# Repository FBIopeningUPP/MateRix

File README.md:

# MateRix Cyberdeck

MateRix is a 10x10 LED Matrix console built around the ESP32-S3. It runs a standalone C++ operating system for embedded games (Tetris, Snake) and connects to a custom PyQt5 desktop application for live telemetry, screen painting, and device configuration over UART.

## Features

* Standalone C++ embedded OS with multitasking state machine
* Playable Tetris and Snake game engines
* Hardware-level Matrix Digital Rain screensaver with idle timeout
* 10x10 WS2812B LED Matrix divided into 4 high-speed hardware quadrants
* Custom Python (PyQt5) desktop studio for live two-way UART communication
* Real-time telemetry broadcasting and remote device configuration
* Open-source hardware and firmware

## Hardware Specifications

* **MCU:** ESP32-S3-Mini
* **Display:** 100x WS2812B LEDs
* **Level Shifter:** 74AHCT125 (3.3V to 5V logic conversion)
* **Inputs:** 4-way D-Pad, 5 Action Buttons (A, B, X, Y, Start)

## Bill of Materials (BoM)

A complete, itemized BOM generated by KiCad can be viewed here: [Production](./production/bom.csv)

## Steps To Reproduce

### Hardware
1. The hardware design files are located in the `hardware/` directory. Send the Gerber files to a manufacturer to produce the PCB.
2. Solder the ESP32-S3-Mini, 74AHCT125, WS2812B LEDs, and tactile buttons.

### Firmware
1. Open the `firmware/` folder in VS Code using the PlatformIO extension.
2. Connect the ESP32-S3 via USB-C and upload the code.

### Software
1. Navigate to the `software/` folder.
2. Run the pre-compiled executable: `software\MateRix_Cyberdeck_Studio.exe`.
3. *(Optional)* To run from source, install dependencies with `pip install pyqt5 pyserial pyautogui` and run `python main.py`.

## Usage of AI

The usage of AI in this project was done with Google Antigravity, which acted as a pair programmer to help debug the C++ firmware, build the Python UI architecture, and verify the hardware pinouts and PCB routing strategies.

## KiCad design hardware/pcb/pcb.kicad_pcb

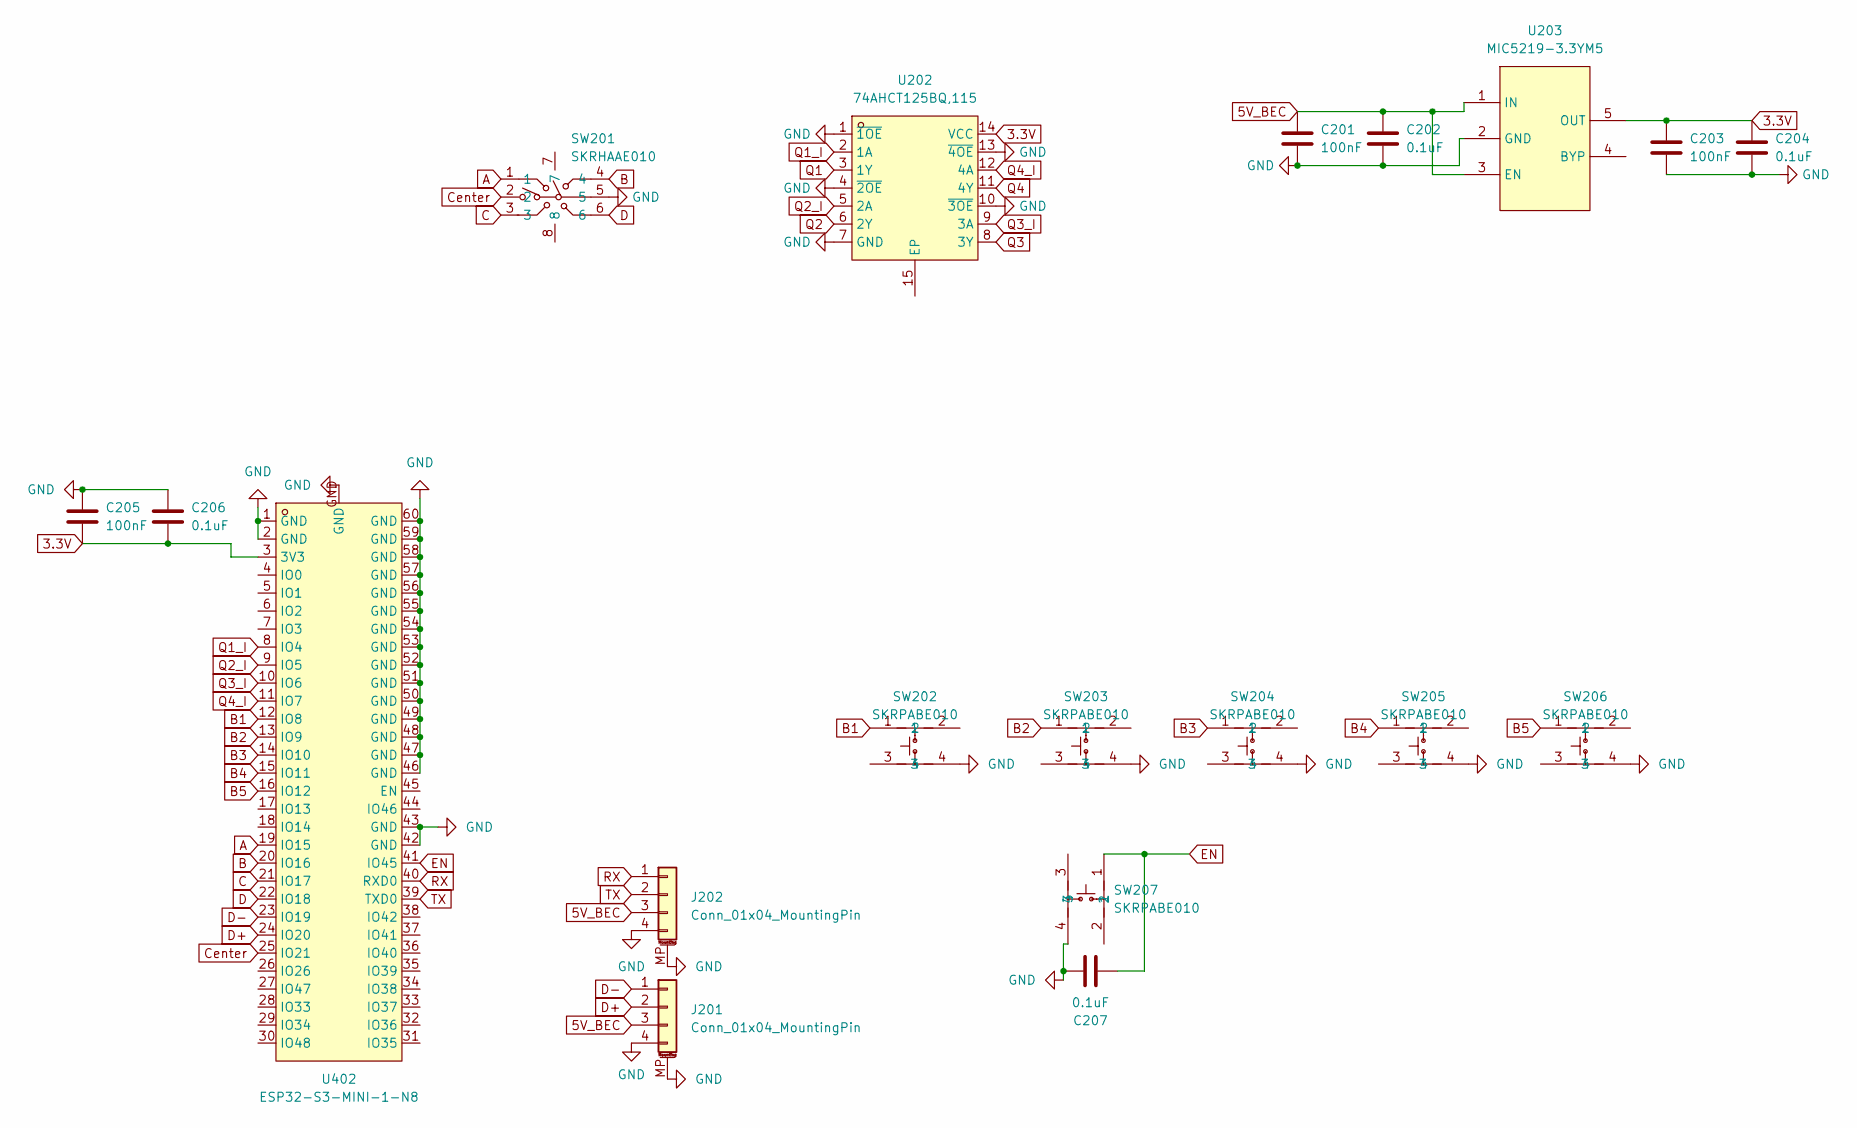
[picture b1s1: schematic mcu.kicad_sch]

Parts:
C201, C203, C205: 100nF; C_0603_1608Metric
C202, C204, C206, C207: 0.1uF; C_0603_1608Metric
J201, J202: Conn_01x04_MountingPin; JST_GH_SM04B-GHS-TB_1x04-1MP_P1.25mm_Horizontal
SW201: SKRHAAE010; SW-SMD_SKRHAAE010; MPN SKRHAAE010; LCSC Part C202423
SW202, SW203, SW204, SW205, SW206, SW207: SKRPABE010; KEY-SMD_4P-L4.2-W3.2-P2.20-LS4.6; LCSC Part C115360
U202: 74AHCT125BQ,115; DHVQFN-14_L3.0-W2.5-P0.50-BL-EP; MPN 74AHCT125BQ,115; LCSC Part C554499
U203: MIC5219-3.3YM5; SOT-23-5_L3.0-W1.7-P0.95-LS2.8-TL; LCSC Part C29613
U402: ESP32-S3-MINI-1-N8; BULETM-SMD_ESP32-S3-MINI-1-N8; MPN ESP32-S3-MINI-1-N8; LCSC Part C2913206

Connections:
3.3V: C203.1, C204.1, C205.2, C206.2, U202.14 (VCC), U203.5 (OUT), U402.3 (3V3)
5V_BEC: C201.1, C202.1, J201.3, J202.3, U203.1 (IN), U203.3 (EN); also elsewhere on the board
A: SW201.1, U402.19 (IO15)
B: SW201.4, U402.20 (IO16)
B1: SW202.1, U402.12 (IO8)
B2: SW203.1, U402.13 (IO9)
B3: SW204.1, U402.14 (IO10)
B4: SW205.1, U402.15 (IO11)
B5: SW206.1, U402.16 (IO12)
C: SW201.3, U402.21 (IO17)
Center: SW201.2, U402.25 (IO21)
D: SW201.6, U402.22 (IO18)
D+: J201.2, U402.24 (IO20)
D-: J201.1, U402.23 (IO19)
EN: C207.2, SW207.1, U402.41 (IO45)
GND: C201.2, C202.2, C203.2, C204.2, C205.1, C206.1, C207.1, J201.4, J201.MP (MountPin), J202.4, J202.MP (MountPin), SW201.5, SW202.4, SW203.4, SW204.4, SW205.4, SW206.4, SW207.4, U202.1 (~1OE), U202.4 (~2OE), U202.7 (GND), U202.10 (~3OE), U202.13 (~4OE), U203.2 (GND), U402.1 (GND), U402.2 (GND), U402.42 (GND), U402.43 (GND), U402.46 (GND), U402.47 (GND), U402.48 (GND), U402.49 (GND), U402.50 (GND), U402.51 (GND), U402.52 (GND), U402.53 (GND), U402.54 (GND), U402.55 (GND), U402.56 (GND), U402.57 (GND), U402.58 (GND), U402.59 (GND), U402.60 (GND), U402.GND; also elsewhere on the board
Q1: U202.3 (1Y); also elsewhere on the board
Q1_I: U202.2 (1A), U402.8 (IO4)
Q2: U202.6 (2Y); also elsewhere on the board
Q2_I: U202.5 (2A), U402.9 (IO5)
Q3: U202.8 (3Y); also elsewhere on the board
Q3_I: U202.9 (3A), U402.10 (IO6)
Q4: U202.11 (4Y); also elsewhere on the board
Q4_I: U202.12 (4A), U402.11 (IO7)
RX: J202.1, U402.40 (RXD0)
TX: J202.2, U402.39 (TXD0)

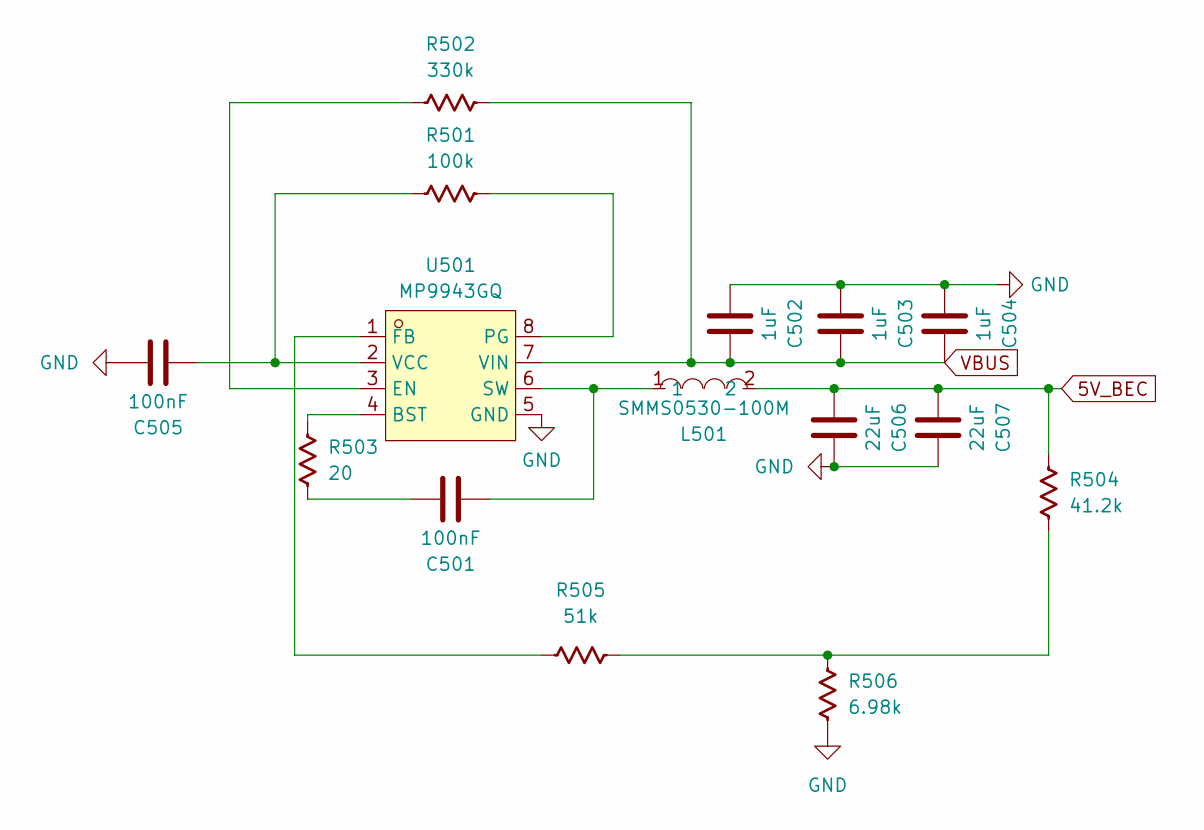
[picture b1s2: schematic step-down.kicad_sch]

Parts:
C501, C505: 100nF; C_0805_2012Metric
C502, C503, C504: 1uF; C_0805_2012Metric
C506, C507: 22uF; C_0805_2012Metric
L501: SMMS0530-100M; IND-SMD_L5.2-W5.2_MCW-0530; MPN SMMS0530-100M; LCSC Part C181721
R501: 100k; R_0603
R502: 330k; R_0603
R503: 20; R_0603
R504: 41.2k; R_0603
R505: 51k; R_0603
R506: 6.98k; R_0603
U501: MP9943GQ; QFN-8_L3.0-W3.0-P0.65-BL; MPN MP9943GQ(TOKMAS); LCSC Part C51889390

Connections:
5V_BEC: C506.2, C507.2, L501.2, R504.2; also elsewhere on the board
GND: C502.2, C503.2, C504.2, C505.1, C506.1, C507.1, R506.2, U501.5 (GND); also elsewhere on the board
unnamed: C501.1, R503.2
unnamed: R504.1, R505.1, R506.1
unnamed: R503.1, U501.4 (BST)
unnamed: R502.2, U501.3 (EN)
unnamed: R505.2, U501.1 (FB)
unnamed: R501.1, U501.8 (PG)
unnamed: C501.2, L501.1, U501.6 (SW)
unnamed: C505.2, R501.2, U501.2 (VCC)
VBUS: C502.1, C503.1, C504.1, R502.1, U501.7 (VIN); also elsewhere on the board

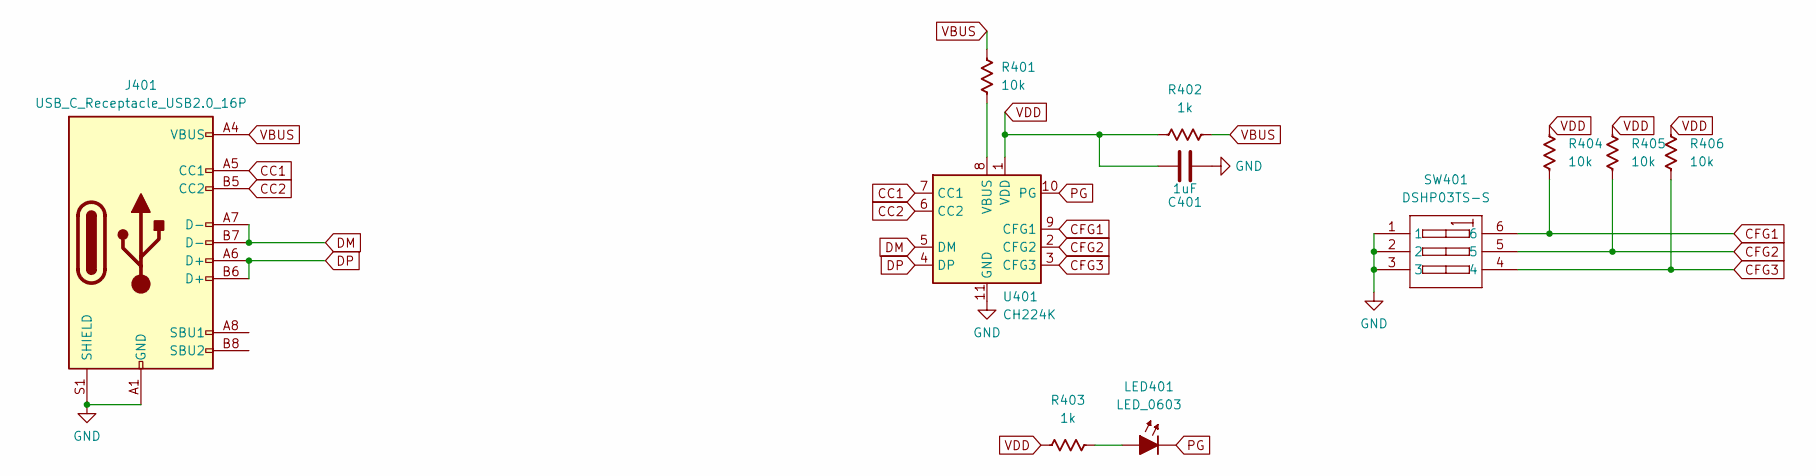
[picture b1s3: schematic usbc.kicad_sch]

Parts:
C401: 1uF; C_0603_1608Metric
J401: USB_C_Receptacle_USB2.0_16P; USB_C_Receptacle_GCT_USB4105-xx-A_16P_TopMnt_Horizontal
LED401: LED_0603; LED_0603_1608Metric
R401, R404, R405, R406: 10k; R_0603
R402, R403: 1k; R_0603
SW401: DSHP03TS-S; SW-SMD_DSHP03TS-S; MPN DSHP03TS-S; LCSC Part C319051
U401: CH224K; SSOP-10-1EP_3.9x4.9mm_P1mm_EP2.1x3.3mm_ThermalVias

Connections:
CC1: J401.A5 (CC1), U401.7 (CC1)
CC2: J401.B5 (CC2), U401.6 (CC2)
CFG1: R404.1, SW401.6, U401.9 (CFG1)
CFG2: R405.1, SW401.5, U401.2 (CFG2)
CFG3: R406.1, SW401.4, U401.3 (CFG3)
DM: J401.A7 (D-), J401.B7 (D-), U401.5 (DM)
DP: J401.A6 (D+), J401.B6 (D+), U401.4 (DP)
GND: C401.2, J401.A1 (GND), J401.A12 (GND), J401.B1 (GND), J401.B12 (GND), J401.S1 (SHIELD), SW401.1, SW401.2, SW401.3, U401.11 (GND); also elsewhere on the board
unnamed: LED401.2 (A), R403.2
unnamed: R401.2, U401.8 (VBUS)
PG: LED401.1 (K), U401.10 (PG)
VBUS: J401.A4 (VBUS), J401.A9 (VBUS), J401.B4 (VBUS), J401.B9 (VBUS), R401.1, R402.2; also elsewhere on the board
VDD: C401.1, R402.1, R403.1, R404.2, R405.2, R406.2, U401.1 (VDD)

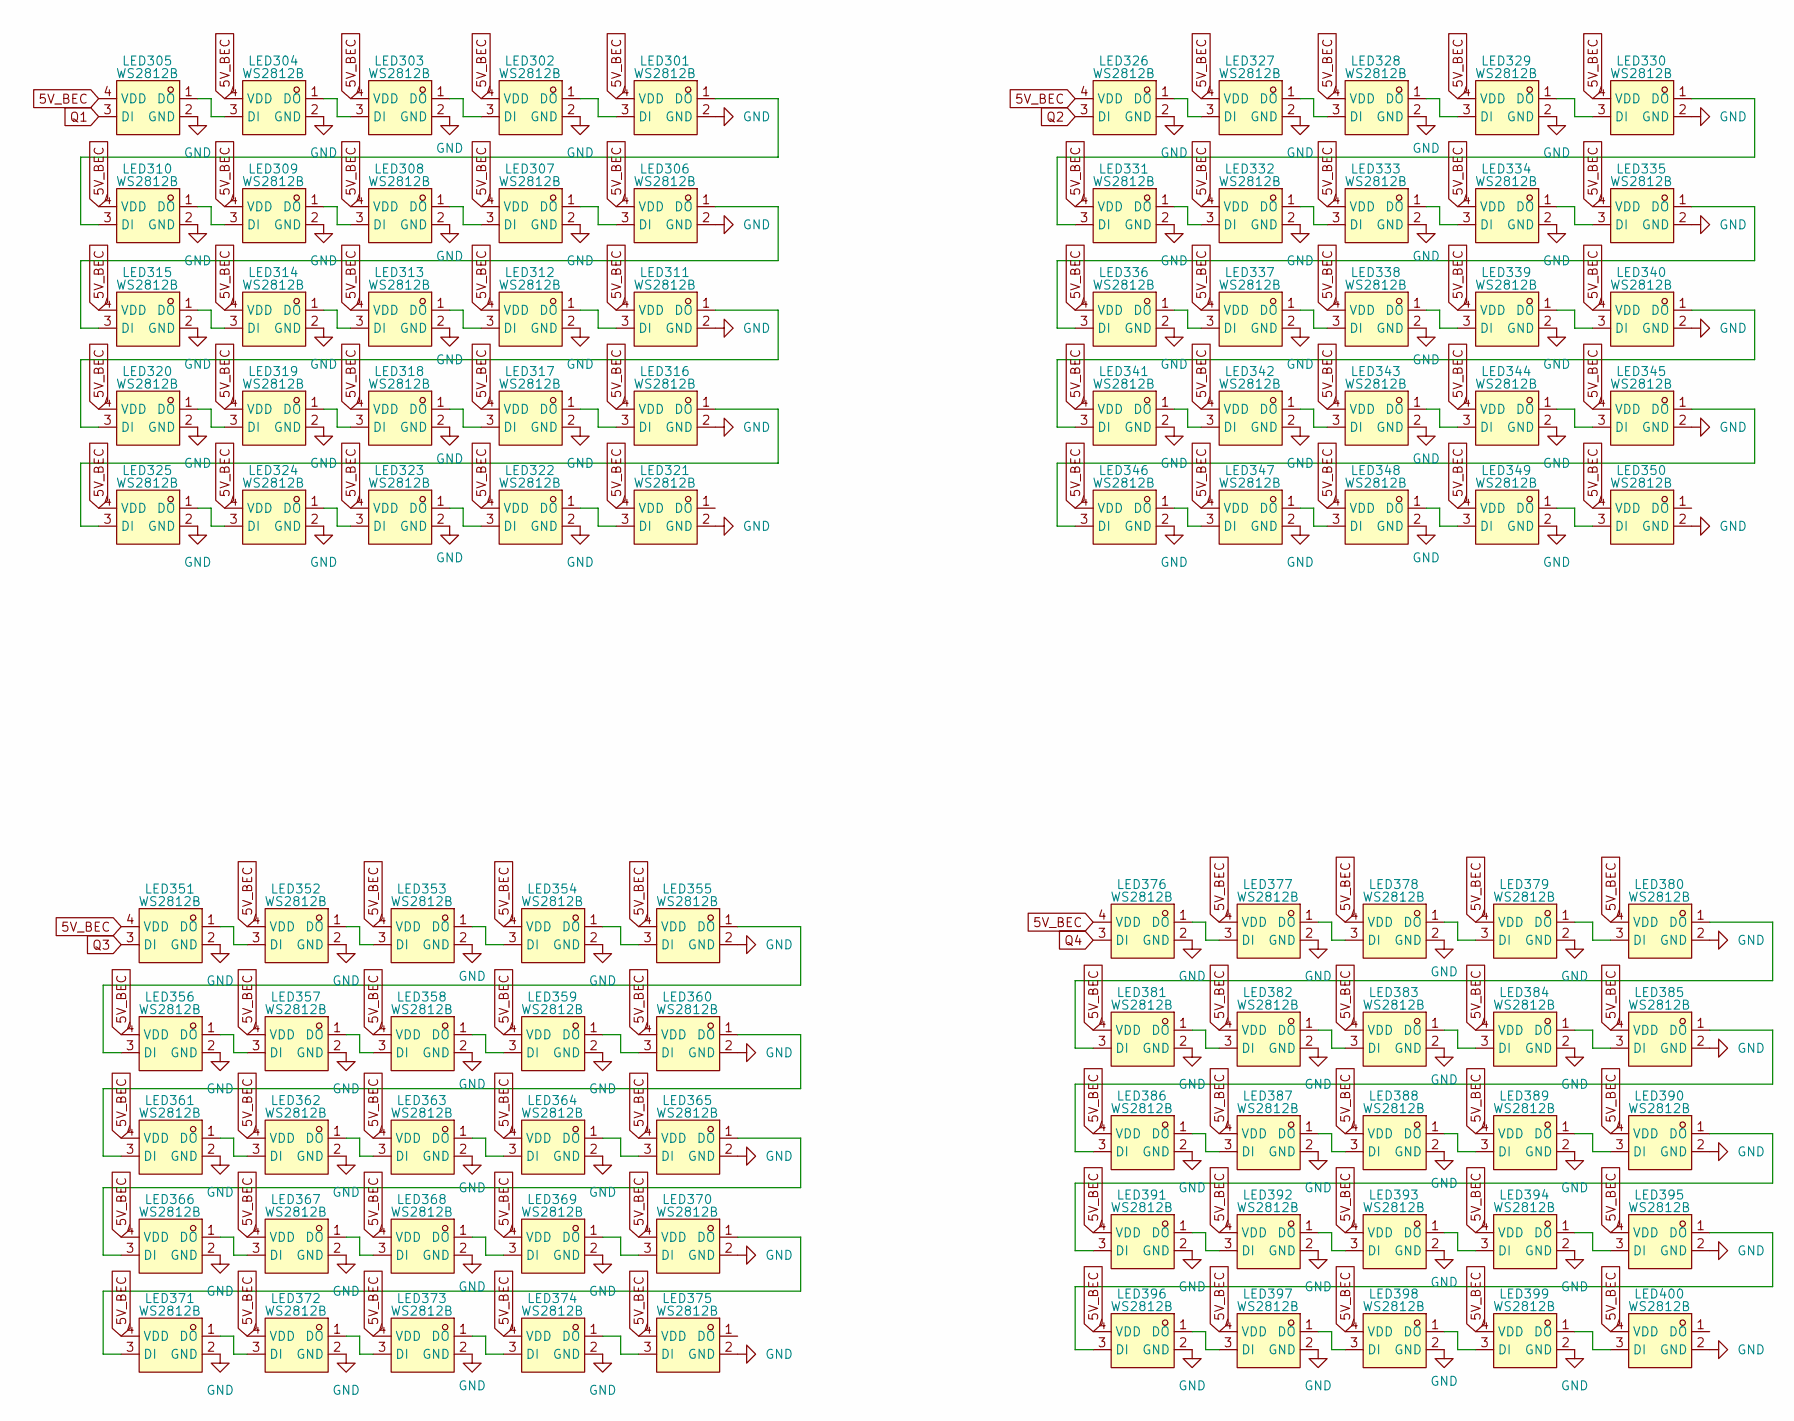
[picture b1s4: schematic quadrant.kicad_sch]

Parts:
LED301, LED302, LED303, LED304, LED305, LED306, LED307, LED308, LED309, LED310, LED311, LED312, LED313, LED314, LED315, LED316, LED317, LED318, LED319, LED320, LED321, LED322, LED323, LED324, LED325, LED326, LED327, LED328, LED329, LED330, LED331, LED332, LED333, LED334, LED335, LED336, LED337, LED338, LED339, LED340, LED341, LED342, LED343, LED344, LED345, LED346, LED347, LED348, LED349, LED350, LED351, LED352, LED353, LED354, LED355, LED356, LED357, LED358, LED359, LED360, LED361, LED362, LED363, LED364, LED365, LED366, LED367, LED368, LED369, LED370, LED371, LED372, LED373, LED374, LED375, LED376, LED377, LED378, LED379, LED380, LED381, LED382, LED383, LED384, LED385, LED386, LED387, LED388, LED389, LED390, LED391, LED392, LED393, LED394, LED395, LED396, LED397, LED398, LED399, LED400: WS2812B; LED-SMD_4P-L2.0-W2.0-TL_WS2812B-2020; MPN WS2812B-2020; LCSC Part C965555

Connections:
5V_BEC: LED301.4 (VDD), LED302.4 (VDD), LED303.4 (VDD), LED304.4 (VDD), LED305.4 (VDD), LED306.4 (VDD), LED307.4 (VDD), LED308.4 (VDD), LED309.4 (VDD), LED310.4 (VDD), LED311.4 (VDD), LED312.4 (VDD), LED313.4 (VDD), LED314.4 (VDD), LED315.4 (VDD), LED316.4 (VDD), LED317.4 (VDD), LED318.4 (VDD), LED319.4 (VDD), LED320.4 (VDD), LED321.4 (VDD), LED322.4 (VDD), LED323.4 (VDD), LED324.4 (VDD), LED325.4 (VDD), LED326.4 (VDD), LED327.4 (VDD), LED328.4 (VDD), LED329.4 (VDD), LED330.4 (VDD), LED331.4 (VDD), LED332.4 (VDD), LED333.4 (VDD), LED334.4 (VDD), LED335.4 (VDD), LED336.4 (VDD), LED337.4 (VDD), LED338.4 (VDD), LED339.4 (VDD), LED340.4 (VDD), LED341.4 (VDD), LED342.4 (VDD), LED343.4 (VDD), LED344.4 (VDD), LED345.4 (VDD), LED346.4 (VDD), LED347.4 (VDD), LED348.4 (VDD), LED349.4 (VDD), LED350.4 (VDD), LED351.4 (VDD), LED352.4 (VDD), LED353.4 (VDD), LED354.4 (VDD), LED355.4 (VDD), LED356.4 (VDD), LED357.4 (VDD), LED358.4 (VDD), LED359.4 (VDD), LED360.4 (VDD), LED361.4 (VDD), LED362.4 (VDD), LED363.4 (VDD), LED364.4 (VDD), LED365.4 (VDD), LED366.4 (VDD), LED367.4 (VDD), LED368.4 (VDD), LED369.4 (VDD), LED370.4 (VDD), LED371.4 (VDD), LED372.4 (VDD), LED373.4 (VDD), LED374.4 (VDD), LED375.4 (VDD), LED376.4 (VDD), LED377.4 (VDD), LED378.4 (VDD), LED379.4 (VDD), LED380.4 (VDD), LED381.4 (VDD), LED382.4 (VDD), LED383.4 (VDD), LED384.4 (VDD), LED385.4 (VDD), LED386.4 (VDD), LED387.4 (VDD), LED388.4 (VDD), LED389.4 (VDD), LED390.4 (VDD), LED391.4 (VDD), LED392.4 (VDD), LED393.4 (VDD), LED394.4 (VDD), LED395.4 (VDD), LED396.4 (VDD), LED397.4 (VDD), LED398.4 (VDD), LED399.4 (VDD), LED400.4 (VDD); also elsewhere on the board
GND: LED301.2 (GND), LED302.2 (GND), LED303.2 (GND), LED304.2 (GND), LED305.2 (GND), LED306.2 (GND), LED307.2 (GND), LED308.2 (GND), LED309.2 (GND), LED310.2 (GND), LED311.2 (GND), LED312.2 (GND), LED313.2 (GND), LED314.2 (GND), LED315.2 (GND), LED316.2 (GND), LED317.2 (GND), LED318.2 (GND), LED319.2 (GND), LED320.2 (GND), LED321.2 (GND), LED322.2 (GND), LED323.2 (GND), LED324.2 (GND), LED325.2 (GND), LED326.2 (GND), LED327.2 (GND), LED328.2 (GND), LED329.2 (GND), LED330.2 (GND), LED331.2 (GND), LED332.2 (GND), LED333.2 (GND), LED334.2 (GND), LED335.2 (GND), LED336.2 (GND), LED337.2 (GND), LED338.2 (GND), LED339.2 (GND), LED340.2 (GND), LED341.2 (GND), LED342.2 (GND), LED343.2 (GND), LED344.2 (GND), LED345.2 (GND), LED346.2 (GND), LED347.2 (GND), LED348.2 (GND), LED349.2 (GND), LED350.2 (GND), LED351.2 (GND), LED352.2 (GND), LED353.2 (GND), LED354.2 (GND), LED355.2 (GND), LED356.2 (GND), LED357.2 (GND), LED358.2 (GND), LED359.2 (GND), LED360.2 (GND), LED361.2 (GND), LED362.2 (GND), LED363.2 (GND), LED364.2 (GND), LED365.2 (GND), LED366.2 (GND), LED367.2 (GND), LED368.2 (GND), LED369.2 (GND), LED370.2 (GND), LED371.2 (GND), LED372.2 (GND), LED373.2 (GND), LED374.2 (GND), LED375.2 (GND), LED376.2 (GND), LED377.2 (GND), LED378.2 (GND), LED379.2 (GND), LED380.2 (GND), LED381.2 (GND), LED382.2 (GND), LED383.2 (GND), LED384.2 (GND), LED385.2 (GND), LED386.2 (GND), LED387.2 (GND), LED388.2 (GND), LED389.2 (GND), LED390.2 (GND), LED391.2 (GND), LED392.2 (GND), LED393.2 (GND), LED394.2 (GND), LED395.2 (GND), LED396.2 (GND), LED397.2 (GND), LED398.2 (GND), LED399.2 (GND), LED400.2 (GND); also elsewhere on the board
unnamed: LED301.3 (DI), LED302.1 (DO)
unnamed: LED301.1 (DO), LED310.3 (DI)
unnamed: LED302.3 (DI), LED303.1 (DO)
unnamed: LED303.3 (DI), LED304.1 (DO)
unnamed: LED304.3 (DI), LED305.1 (DO)
unnamed: LED306.3 (DI), LED307.1 (DO)
unnamed: LED306.1 (DO), LED315.3 (DI)
unnamed: LED307.3 (DI), LED308.1 (DO)
unnamed: LED308.3 (DI), LED309.1 (DO)
unnamed: LED309.3 (DI), LED310.1 (DO)
unnamed: LED311.3 (DI), LED312.1 (DO)
unnamed: LED311.1 (DO), LED320.3 (DI)
unnamed: LED312.3 (DI), LED313.1 (DO)
unnamed: LED313.3 (DI), LED314.1 (DO)
unnamed: LED314.3 (DI), LED315.1 (DO)
unnamed: LED316.3 (DI), LED317.1 (DO)
unnamed: LED316.1 (DO), LED325.3 (DI)
unnamed: LED317.3 (DI), LED318.1 (DO)
unnamed: LED318.3 (DI), LED319.1 (DO)
unnamed: LED319.3 (DI), LED320.1 (DO)
unnamed: LED321.3 (DI), LED322.1 (DO)
unnamed: LED322.3 (DI), LED323.1 (DO)
unnamed: LED323.3 (DI), LED324.1 (DO)
unnamed: LED324.3 (DI), LED325.1 (DO)
unnamed: LED326.1 (DO), LED327.3 (DI)
unnamed: LED327.1 (DO), LED328.3 (DI)
unnamed: LED328.1 (DO), LED329.3 (DI)
unnamed: LED329.1 (DO), LED330.3 (DI)
unnamed: LED330.1 (DO), LED331.3 (DI)
unnamed: LED331.1 (DO), LED332.3 (DI)
unnamed: LED332.1 (DO), LED333.3 (DI)
unnamed: LED333.1 (DO), LED334.3 (DI)
unnamed: LED334.1 (DO), LED335.3 (DI)
unnamed: LED335.1 (DO), LED336.3 (DI)
unnamed: LED336.1 (DO), LED337.3 (DI)
unnamed: LED337.1 (DO), LED338.3 (DI)
unnamed: LED338.1 (DO), LED339.3 (DI)
unnamed: LED339.1 (DO), LED340.3 (DI)
unnamed: LED340.1 (DO), LED341.3 (DI)
unnamed: LED341.1 (DO), LED342.3 (DI)
unnamed: LED342.1 (DO), LED343.3 (DI)
unnamed: LED343.1 (DO), LED344.3 (DI)
unnamed: LED344.1 (DO), LED345.3 (DI)
unnamed: LED345.1 (DO), LED346.3 (DI)
unnamed: LED346.1 (DO), LED347.3 (DI)
unnamed: LED347.1 (DO), LED348.3 (DI)
unnamed: LED348.1 (DO), LED349.3 (DI)
unnamed: LED349.1 (DO), LED350.3 (DI)
unnamed: LED351.1 (DO), LED352.3 (DI)
unnamed: LED352.1 (DO), LED353.3 (DI)
unnamed: LED353.1 (DO), LED354.3 (DI)
unnamed: LED354.1 (DO), LED355.3 (DI)
unnamed: LED355.1 (DO), LED356.3 (DI)
unnamed: LED356.1 (DO), LED357.3 (DI)
unnamed: LED357.1 (DO), LED358.3 (DI)
unnamed: LED358.1 (DO), LED359.3 (DI)
unnamed: LED359.1 (DO), LED360.3 (DI)
unnamed: LED360.1 (DO), LED361.3 (DI)
unnamed: LED361.1 (DO), LED362.3 (DI)
unnamed: LED362.1 (DO), LED363.3 (DI)
unnamed: LED363.1 (DO), LED364.3 (DI)
unnamed: LED364.1 (DO), LED365.3 (DI)
unnamed: LED365.1 (DO), LED366.3 (DI)
unnamed: LED366.1 (DO), LED367.3 (DI)
unnamed: LED367.1 (DO), LED368.3 (DI)
unnamed: LED368.1 (DO), LED369.3 (DI)
unnamed: LED369.1 (DO), LED370.3 (DI)
unnamed: LED370.1 (DO), LED371.3 (DI)
unnamed: LED371.1 (DO), LED372.3 (DI)
unnamed: LED372.1 (DO), LED373.3 (DI)
unnamed: LED373.1 (DO), LED374.3 (DI)
unnamed: LED374.1 (DO), LED375.3 (DI)
unnamed: LED376.1 (DO), LED377.3 (DI)
unnamed: LED377.1 (DO), LED378.3 (DI)
unnamed: LED378.1 (DO), LED379.3 (DI)
unnamed: LED379.1 (DO), LED380.3 (DI)
unnamed: LED380.1 (DO), LED381.3 (DI)
unnamed: LED381.1 (DO), LED382.3 (DI)
unnamed: LED382.1 (DO), LED383.3 (DI)
unnamed: LED383.1 (DO), LED384.3 (DI)
unnamed: LED384.1 (DO), LED385.3 (DI)
unnamed: LED385.1 (DO), LED386.3 (DI)
unnamed: LED386.1 (DO), LED387.3 (DI)
unnamed: LED387.1 (DO), LED388.3 (DI)
unnamed: LED388.1 (DO), LED389.3 (DI)
unnamed: LED389.1 (DO), LED390.3 (DI)
unnamed: LED390.1 (DO), LED391.3 (DI)
unnamed: LED391.1 (DO), LED392.3 (DI)
unnamed: LED392.1 (DO), LED393.3 (DI)
unnamed: LED393.1 (DO), LED394.3 (DI)
unnamed: LED394.1 (DO), LED395.3 (DI)
unnamed: LED395.1 (DO), LED396.3 (DI)
unnamed: LED396.1 (DO), LED397.3 (DI)
unnamed: LED397.1 (DO), LED398.3 (DI)
unnamed: LED398.1 (DO), LED399.3 (DI)
unnamed: LED399.1 (DO), LED400.3 (DI)
Q1: LED305.3 (DI); also elsewhere on the board
Q2: LED326.3 (DI); also elsewhere on the board
Q3: LED351.3 (DI); also elsewhere on the board
Q4: LED376.3 (DI); also elsewhere on the board

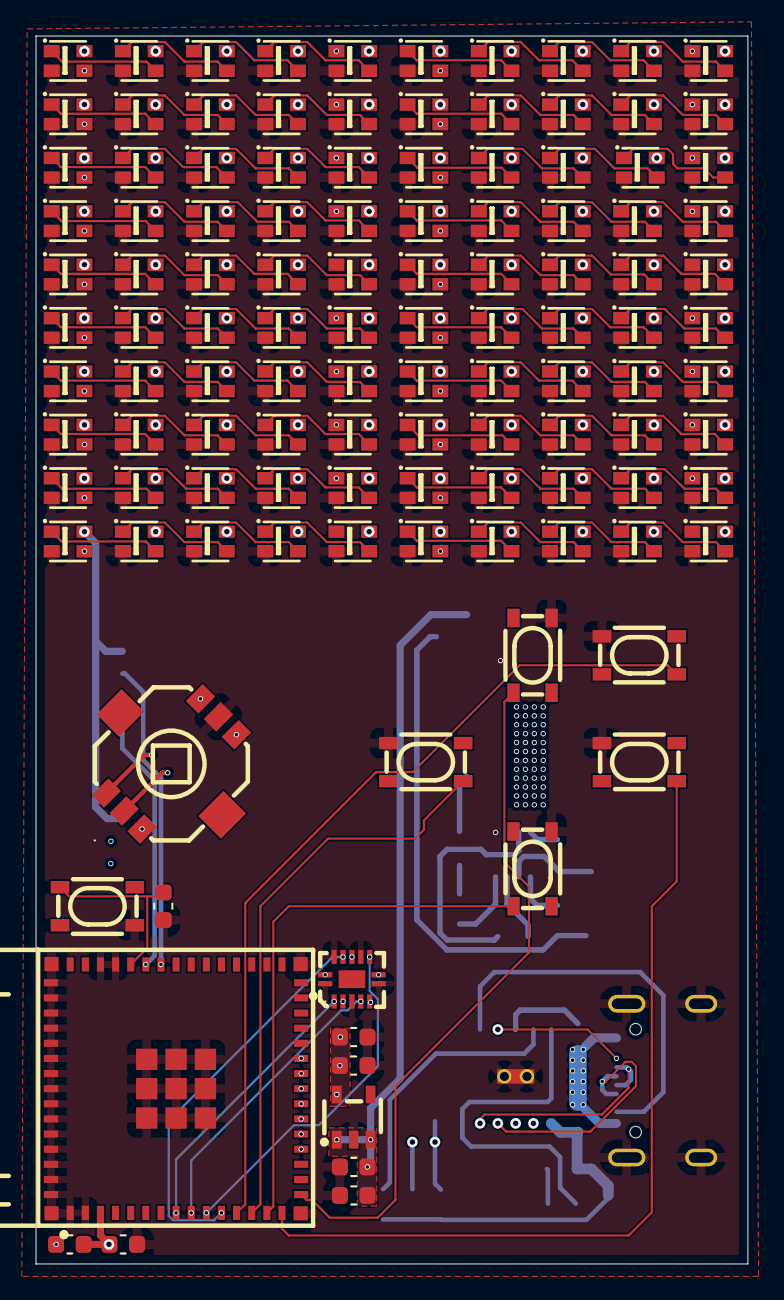
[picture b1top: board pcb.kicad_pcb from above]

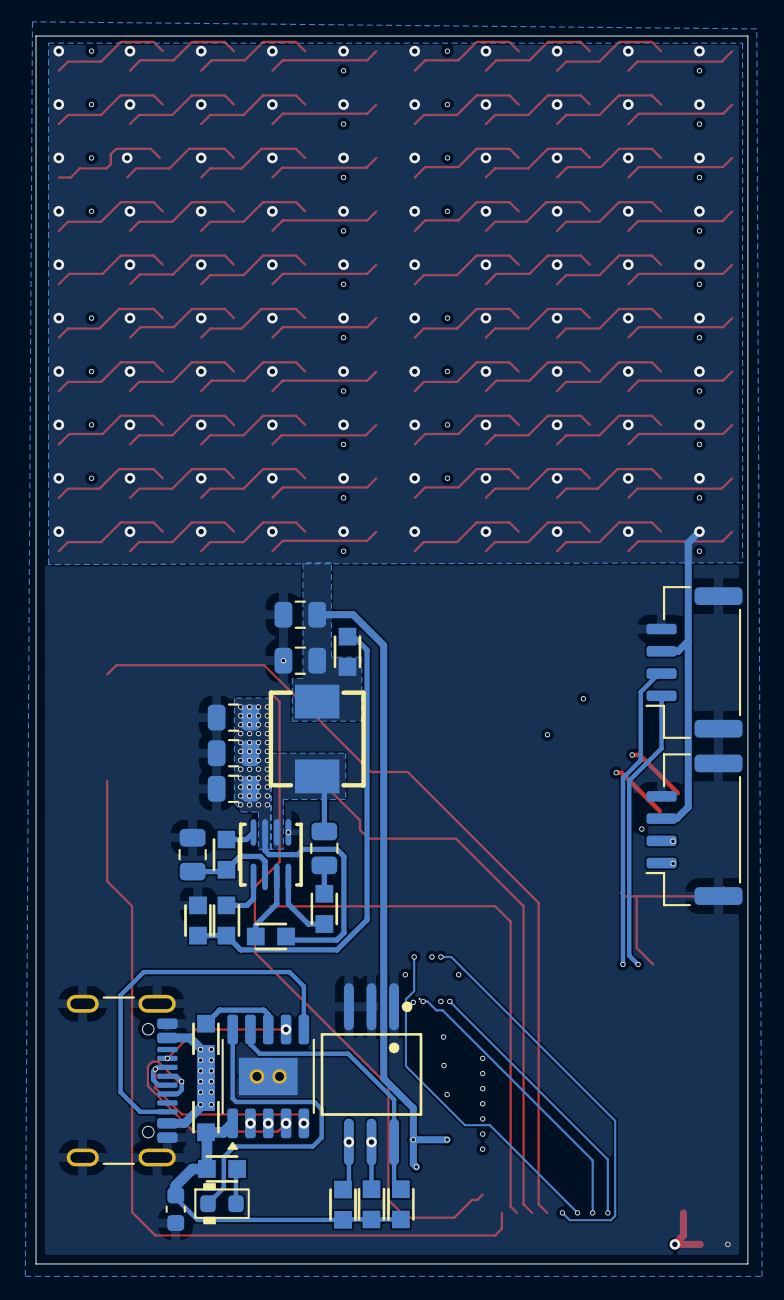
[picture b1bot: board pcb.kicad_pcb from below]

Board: 4 copper layers, 40.0 x 69.0 mm, 145 parts (28 on the bottom side), 142 nets.

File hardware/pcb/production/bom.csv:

Designator,Footprint,Quantity,Value,LCSC Part #
"C201, C203, C205",0603,3,100nF,
"C202, C204, C206, C207",0603,4,0.1uF,
C401,0603,1,1uF,
"C501, C505",0805,2,100nF,
"C502, C503, C504",0805,3,1uF,
"C506, C507",0805,2,22uF,
"J201, J202",JST_GH_SM04B-GHS-TB_1x04-1MP_P1.25mm_Horizontal,2,Conn_01x04_MountingPin,
J401,USB_C_Receptacle_GCT_USB4105-xx-A_16P_TopMnt_Horizontal,1,USB_C_Receptacle_USB2.0_16P,
L501,IND-SMD_L5.2-W5.2_MCW-0530,1,SMMS0530-100M,C181721
"LED301, LED302, LED303, LED304, LED305, LED306, LED307, LED308, LED309, LED310, LED311, LED312, LED313, LED314, LED315, LED316, LED317, LED318, LED319, LED320, LED321, LED322, LED323, LED324, LED325, LED326, LED327, LED328, LED329, LED330, LED331, LED332, LED333, LED334, LED335, LED336, LED337, LED338, LED339, LED340, LED341, LED342, LED343, LED344, LED345, LED346, LED347, LED348, LED349, LED350, LED351, LED352, LED353, LED354, LED355, LED356, LED357, LED358, LED359, LED360, LED361, LED362, LED363, LED364, LED365, LED366, LED367, LED368, LED369, LED370, LED371, LED372, LED373, LED374, LED375, LED376, LED377, LED378, LED379, LED380, LED381, LED382, LED383, LED384, LED385, LED386, LED387, LED388, LED389, LED390, LED391, LED392, LED393, LED394, LED395, LED396, LED397, LED398, LED399, LED400",LED-SMD_4P-L2.0-W2.0-TL_WS2812B-2020,100,WS2812B,C965555
LED401,0603,1,LED_0603,
"R401, R404, R405, R406",R_0603,4,10k,
"R402, R403",R_0603,2,1k,
R501,R_0603,1,100k,
R502,R_0603,1,330k,
R503,R_0603,1,20,
R504,R_0603,1,41.2k,
R505,R_0603,1,51k,
R506,R_0603,1,6.98k,
SW201,SW-SMD_SKRHAAE010,1,SKRHAAE010,C202423
"SW202, SW203, SW204, SW205, SW206, SW207",KEY-SMD_4P-L4.2-W3.2-P2.20-LS4.6,6,SKRPABE010,C115360
SW401,SW-SMD_DSHP03TS-S,1,DSHP03TS-S,C319051
U202,DHVQFN-14_L3.0-W2.5-P0.50-BL-EP,1,"74AHCT125BQ,115",C554499
U203,SOT-23-5_L3.0-W1.7-P0.95-LS2.8-TL,1,MIC5219-3.3YM5,C29613
U401,SSOP-10-1EP_3.9x4.9mm_P1mm_EP2.1x3.3mm_ThermalVias,1,CH224K,
U402,BULETM-SMD_ESP32-S3-MINI-1-N8,1,ESP32-S3-MINI-1-N8,C2913206
U501,QFN-8_L3.0-W3.0-P0.65-BL,1,MP9943GQ,C51889390
